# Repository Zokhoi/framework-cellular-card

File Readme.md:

## Framework Cellular Expansion Card

Compatible with Quectel cellular modules with same pinout as BG96.

This PCB design has been tested with EG912U-GL and EG95-EX modules. Other modules with compatible pinout will need different component values in various positions, consult the relevant hardware design information for details.

This PCB design is in alpha state, therefore gerber will not be provided and you should only proceed ordering at your own risk.

This PCB design does not incorporate built in antennas, and instead includes MHF-1 connectors for LTE main, diversity and GNSS. Thus you should pair your own 50 ohms impedance LTE antenna.

The PCB is 15mm longer than a regular expansion card PCB, a preliminary case design is provided.

### Board specifications

Size 26mm x 45mm, thickness 0.8mm, 4 layers, copper thickness 1oz 0.5oz 0.5oz 1oz, impedance controlled board with 0.2mm prepreg

### Compatible modem series comparison

| Modem series | Cellular standards | Downlink speed | Uplink speed | Cost   |
|--------------|--------------------|----------------|--------------|--------|
| EG95         | 4G, 3G, 2G         | 150 Mb/s       |  50 Mb/s     | \$\$   |
| EG91         | 4G, 2G             |  10 Mb/s       |   5 Mb/s     | \$     |
| BG96         | Cat-M, Cat-NB1     | 375 Kb/s       | 375 Kb/s     | \$\$   |

### License
This hardware design is licensed under [CERN-OHL-W V2 or later](License.txt).

### Board preview

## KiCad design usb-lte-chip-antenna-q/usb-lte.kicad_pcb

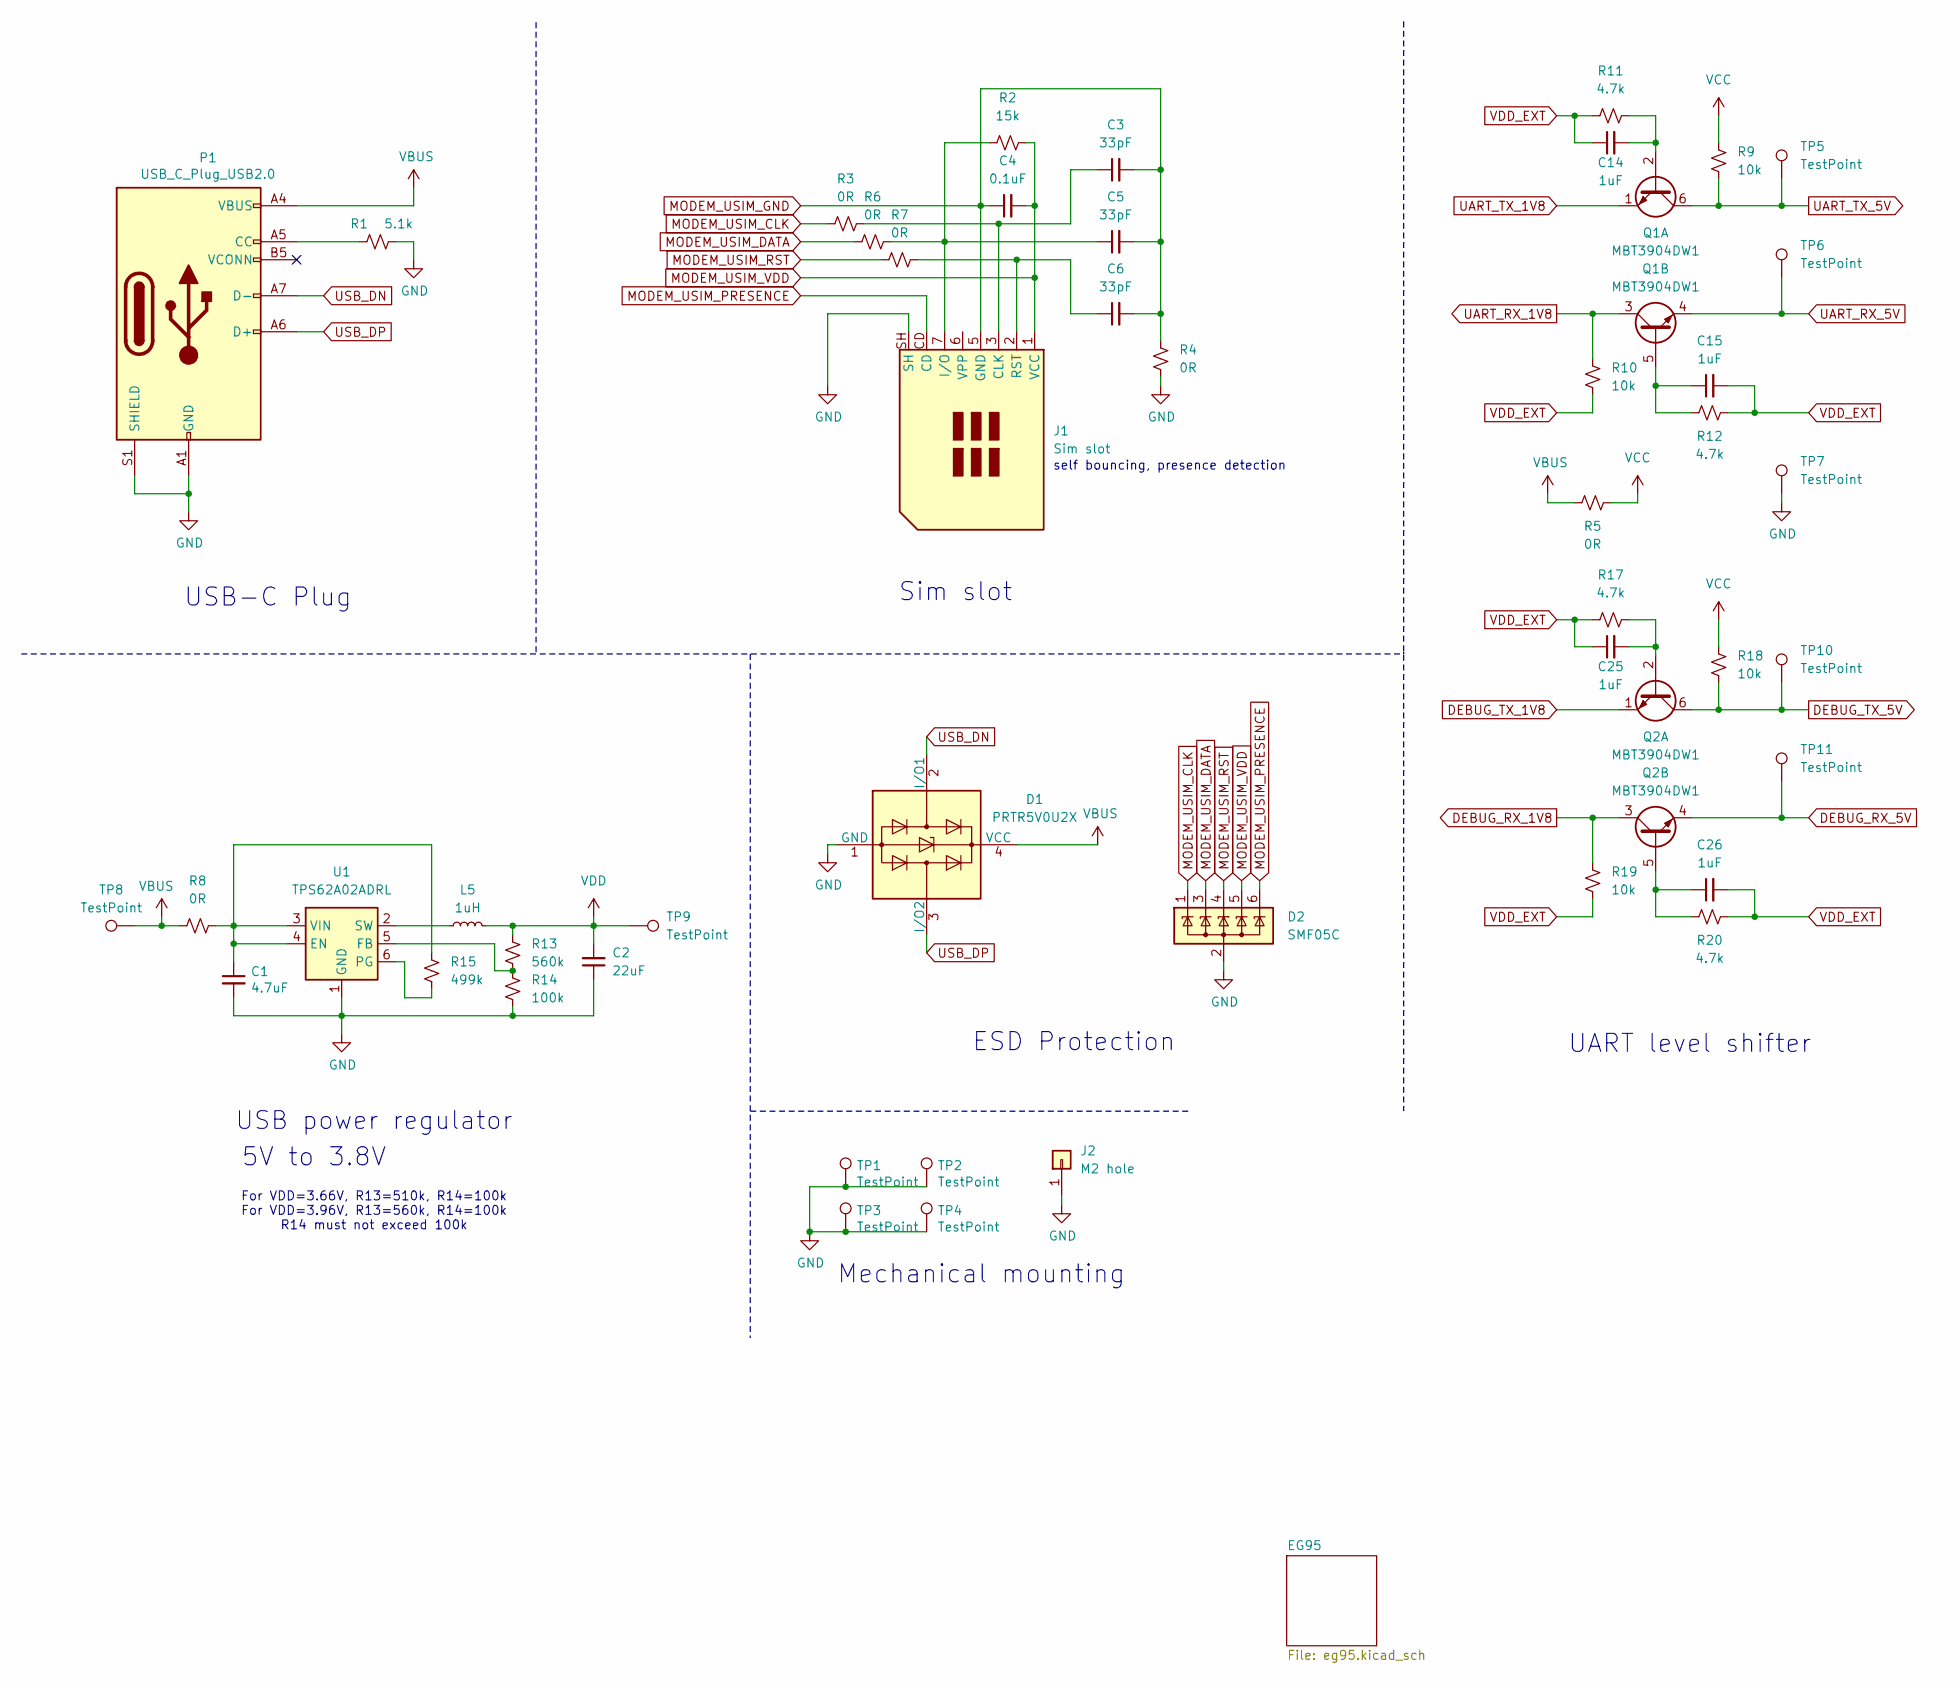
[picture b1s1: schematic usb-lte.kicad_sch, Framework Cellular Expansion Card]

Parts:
C1: 4.7uF; C_0805_2012Metric
C2: 22uF; C_0805_2012Metric
C3, C5, C6: 33pF; C_0402_1005Metric
C4: 0.1uF; C_0402_1005Metric
C14, C15, C25, C26: 1uF; C_0402_1005Metric
D1: PRTR5V0U2X; SOT-143
D2: SMF05C; SOT-363_SC-70-6
J1: Sim slot; SIM_Card_Self_Bounce_Detection
J2: M2 hole; M2_Mount_2.2mm_Pad_Minimal
L5: 1uH; L_APV_ANR252012
P1: USB_C_Plug_USB2.0; USB_C_Plug_Molex_105444
Q1, Q2: MBT3904DW1; SOT-363_SC-70-6
R1: 5.1k; R_0402_1005Metric_Pad0.72x0.64mm_HandSolder
R2: 15k; R_0402_1005Metric
R3, R6, R7, R8: 0R; R_0402_1005Metric_Pad0.72x0.64mm_HandSolder
R4, R5: 0R; R_0402_1005Metric
R9, R10, R18, R19: 10k; R_0402_1005Metric
R11, R12, R17, R20: 4.7k; R_0402_1005Metric
R13: 560k; R_0402_1005Metric
R14: 100k; R_0402_1005Metric
R15: 499k; R_0402_1005Metric
TP1, TP2, TP3, TP4: TestPoint; TestPoint_Pad_1.5x1.5mm
TP5, TP6, TP7, TP8, TP9, TP10, TP11: TestPoint; TestPoint_Pad_1mm
U1: TPS62A02ADRL; SOT-563

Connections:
DEBUG_RX_1V8: Q2.3 (C2), R19.1; also elsewhere on the board
DEBUG_RX_5V: Q2.4 (E2), TP11.1
DEBUG_TX_1V8: Q2.1 (E1); also elsewhere on the board
DEBUG_TX_5V: Q2.6 (C1), R18.2, TP10.1
GND: C1.2, C2.1, D1.1 (GND), D2.2 (A), J1.SH, J2.1, P1.A1 (GND), P1.A12 (GND), P1.B1 (GND), P1.B12 (GND), P1.S1 (SHIELD), R1.2, R4.2, R14.2, TP1.1, TP2.1, TP3.1, TP4.1, TP7.1, U1.1 (GND); also elsewhere on the board
MODEM_USIM_CLK: D2.1 (K), R3.1; also elsewhere on the board
MODEM_USIM_DATA: D2.3 (K), R6.1; also elsewhere on the board
MODEM_USIM_GND: C3.2, C4.1, C5.2, C6.2, J1.5 (GND), R4.1; also elsewhere on the board
MODEM_USIM_PRESENCE: D2.6 (K), J1.CD; also elsewhere on the board
MODEM_USIM_RST: D2.4 (K), R7.1; also elsewhere on the board
MODEM_USIM_VDD: C4.2, D2.5 (K), J1.1 (VCC), R2.2; also elsewhere on the board
unnamed: C3.1, J1.3 (CLK), R3.2
unnamed: C5.1, J1.7 (I/O), R2.1, R6.2
unnamed: C6.1, J1.2 (RST), R7.2
unnamed: P1.A5 (CC), R1.1
unnamed: C14.2, Q1.2 (B1), R11.2
unnamed: C15.1, Q1.5 (B2), R12.1
unnamed: C25.2, Q2.2 (B1), R17.2
unnamed: C26.1, Q2.5 (B2), R20.1
unnamed: C1.1, R8.2, R15.2, U1.3 (VIN), U1.4 (EN)
unnamed: R13.2, R14.1, U1.5 (FB)
unnamed: R15.1, U1.6 (PG)
unnamed: L5.1, U1.2 (SW)
UART_RX_1V8: Q1.3 (C2), R10.1; also elsewhere on the board
UART_RX_5V: Q1.4 (E2), TP6.1
UART_TX_1V8: Q1.1 (E1); also elsewhere on the board
UART_TX_5V: Q1.6 (C1), R9.2, TP5.1
USB_DN: D1.2 (I/O1), P1.A7 (D-); also elsewhere on the board
USB_DP: D1.3 (I/O2), P1.A6 (D+); also elsewhere on the board
VBUS: D1.4 (VCC), P1.A4 (VBUS), P1.A9 (VBUS), P1.B4 (VBUS), P1.B9 (VBUS), R5.1, R8.1, TP8.1; also elsewhere on the board
VCC: R5.2, R9.1, R18.1
VDD: C2.2, L5.2, R13.1, TP9.1; also elsewhere on the board
VDD_EXT: C14.1, C15.2, C25.1, C26.2, R10.2, R11.1, R12.2, R17.1, R19.2, R20.2; also elsewhere on the board

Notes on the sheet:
Sim slot
USB power regulator
For VDD=3.66V, R13=510k, R14=100k For VDD=3.96V, R13=560k, R14=100k R14 must not exceed 100k
Mechanical mounting
self bouncing, presence detection
USB-C Plug
ESD Protection
UART level shifter
5V to 3.8V

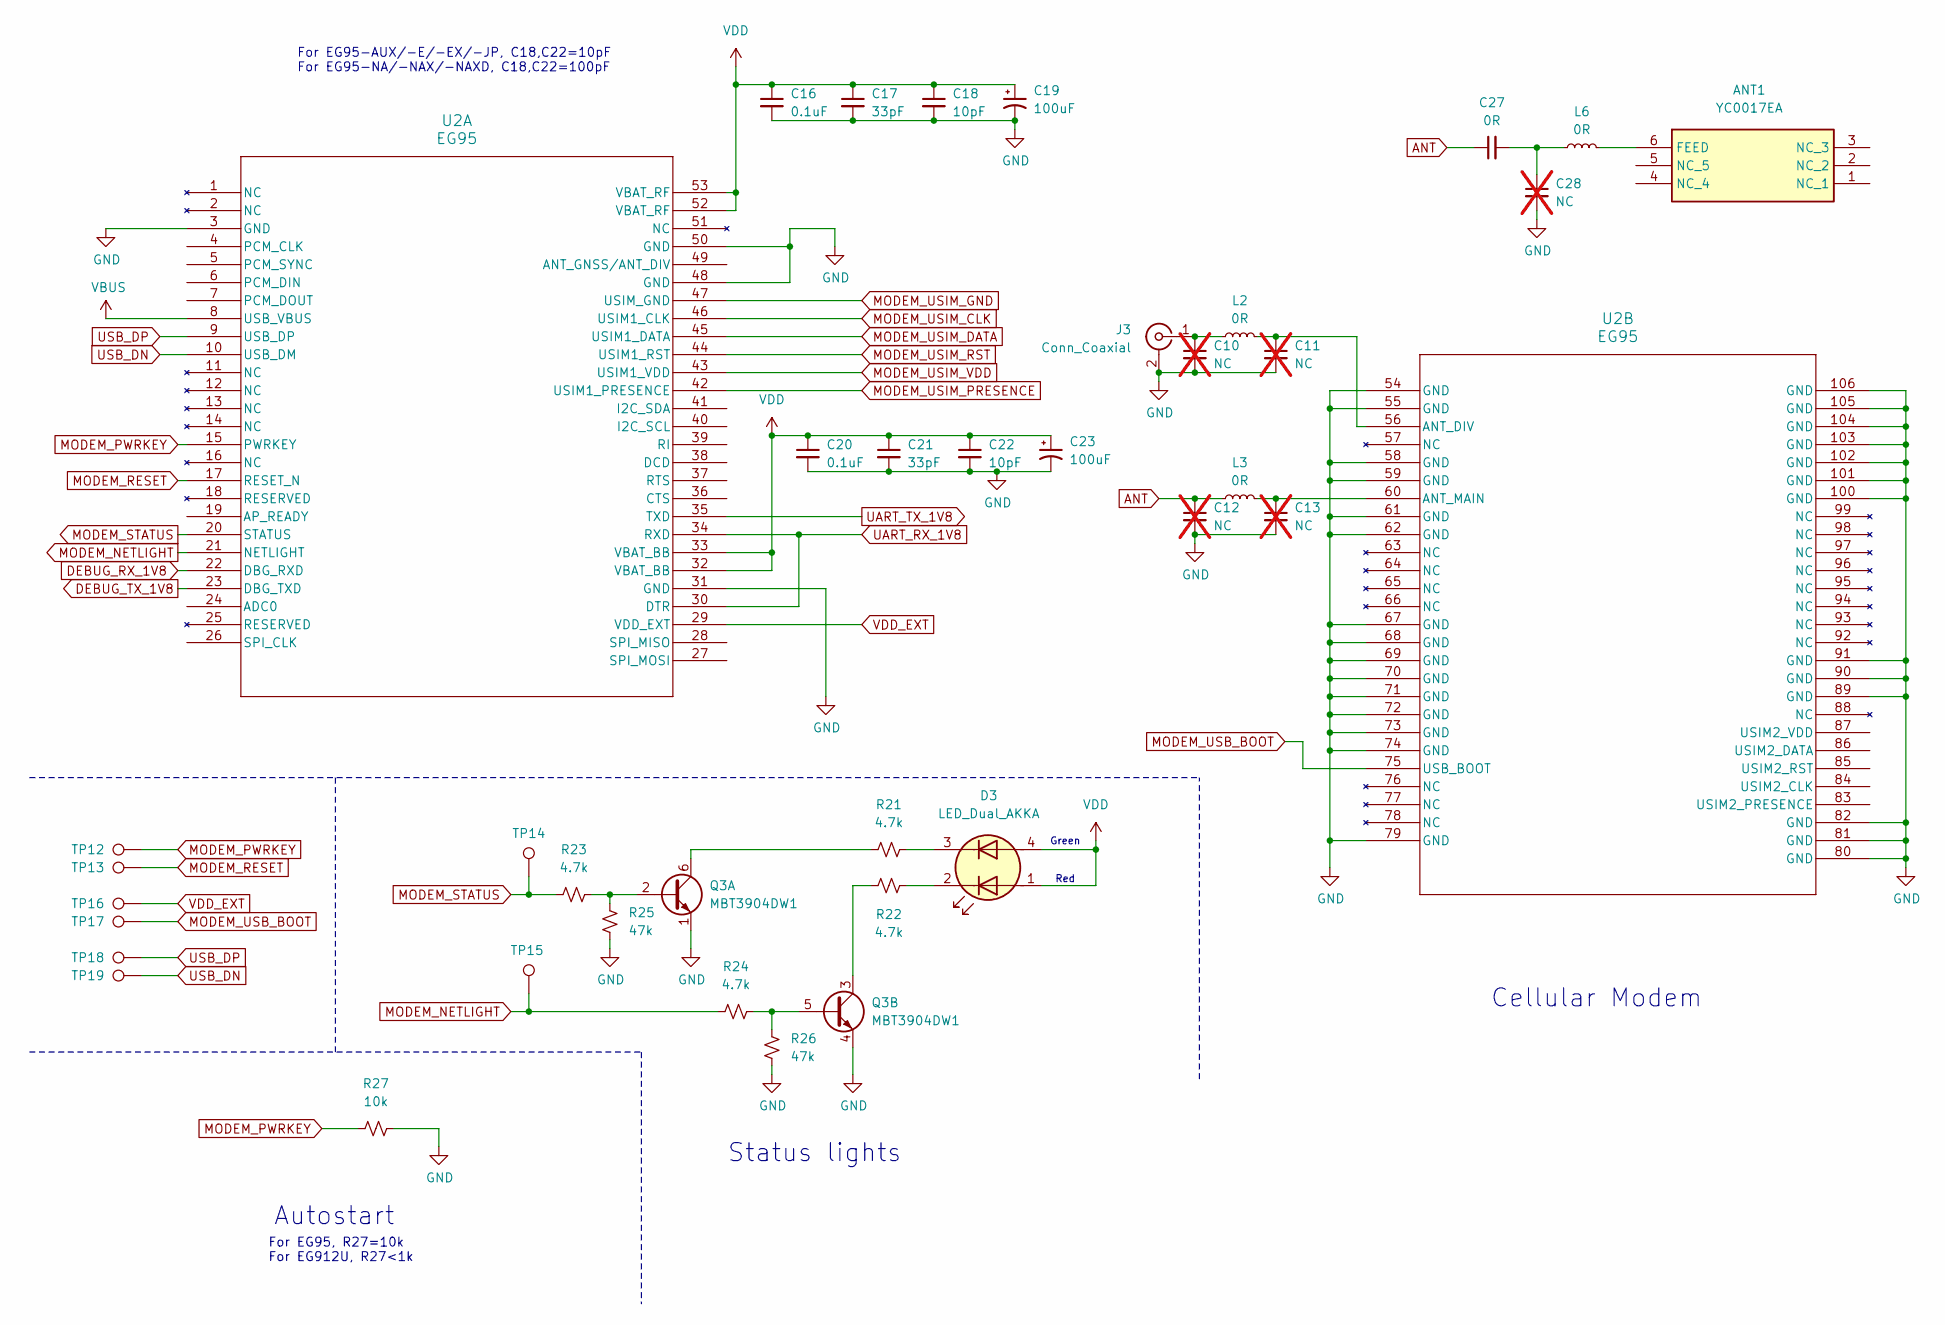
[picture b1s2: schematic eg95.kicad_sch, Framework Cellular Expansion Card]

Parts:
ANT1: YC0017EA; Mouser Part Number 277-YC0017EA
C10, C11, C12, C13, C28: NC; C_0402_1005Metric; not fitted
C16, C20: 0.1uF; C_0402_1005Metric
C17, C21: 33pF; C_0402_1005Metric
C18, C22: 10pF; C_0402_1005Metric
C19, C23: 100uF; CP_EIA-3528-21_Kemet-B
C27: 0R; C_0402_1005Metric
D3: LED_Dual_AKKA; LED_Dual_0805_4pin
J3: Conn_Coaxial; U.FL_Molex_MCRF_73412-0110_Vertical
L2, L3, L6: 0R; L_0402_1005Metric
Q3: MBT3904DW1; SOT-363_SC-70-6
R21, R22, R23, R24: 4.7k; R_0402_1005Metric
R25, R26: 47k; R_0402_1005Metric
R27: 10k; R_0402_1005Metric
TP12, TP13, TP14, TP15, TP16, TP17, TP18, TP19: TestPoint; TestPoint_Pad_1mm
U2: EG95; EG95_QWS

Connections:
ANT: C12.1, C27.1, L3.1
DEBUG_RX_1V8: U2.22 (DBG_RXD); also elsewhere on the board
DEBUG_TX_1V8: U2.23 (DBG_TXD); also elsewhere on the board
GND: C10.2, C11.2, C12.2, C13.2, C16.2, C17.2, C18.2, C19.2, C20.2, C21.2, C22.2, C23.2, C28.2, J3.2 (Ext), Q3.1 (E1), Q3.4 (E2), R25.1, R26.1, R27.1, U2.3 (GND), U2.31 (GND), U2.48 (GND), U2.50 (GND), U2.54 (GND), U2.55 (GND), U2.58 (GND), U2.59 (GND), U2.61 (GND), U2.62 (GND), U2.67 (GND), U2.68 (GND), U2.69 (GND), U2.70 (GND), U2.71 (GND), U2.72 (GND), U2.73 (GND), U2.74 (GND), U2.79 (GND), U2.80 (GND), U2.81 (GND), U2.82 (GND), U2.89 (GND), U2.90 (GND), U2.91 (GND), U2.100 (GND), U2.101 (GND), U2.102 (GND), U2.103 (GND), U2.104 (GND), U2.105 (GND), U2.106 (GND); also elsewhere on the board
MODEM_NETLIGHT: R24.2, TP15.1, U2.21 (NETLIGHT)
MODEM_PWRKEY: R27.2, TP12.1, U2.15 (PWRKEY)
MODEM_RESET: TP13.1, U2.17 (RESET_N)
MODEM_STATUS: R23.2, TP14.1, U2.20 (STATUS)
MODEM_USB_BOOT: TP17.1, U2.75 (USB_BOOT)
MODEM_USIM_CLK: U2.46 (USIM1_CLK); also elsewhere on the board
MODEM_USIM_DATA: U2.45 (USIM1_DATA); also elsewhere on the board
MODEM_USIM_GND: U2.47 (USIM_GND); also elsewhere on the board
MODEM_USIM_PRESENCE: U2.42 (USIM1_PRESENCE); also elsewhere on the board
MODEM_USIM_RST: U2.44 (USIM1_RST); also elsewhere on the board
MODEM_USIM_VDD: U2.43 (USIM1_VDD); also elsewhere on the board
unnamed: ANT1.6 (FEED), L6.2
unnamed: C27.2, C28.1, L6.1
unnamed: D3.2 (K1), R22.1
unnamed: D3.3 (K2), R21.1
unnamed: C10.1, J3.1 (In), L2.1
unnamed: Q3.2 (B1), R23.1, R25.2
unnamed: Q3.6 (C1), R21.2
unnamed: Q3.5 (B2), R24.1, R26.2
unnamed: Q3.3 (C2), R22.2
unnamed: C11.1, L2.2, U2.56 (ANT_DIV)
unnamed: C13.1, L3.2, U2.60 (ANT_MAIN)
UART_RX_1V8: U2.30 (DTR), U2.34 (RXD); also elsewhere on the board
UART_TX_1V8: U2.35 (TXD); also elsewhere on the board
USB_DN: TP19.1, U2.10 (USB_DM); also elsewhere on the board
USB_DP: TP18.1, U2.9 (USB_DP); also elsewhere on the board
VBUS: U2.8 (USB_VBUS); also elsewhere on the board
VDD: C16.1, C17.1, C18.1, C19.1, C20.1, C21.1, C22.1, C23.1, D3.1 (A1), D3.4 (A2), U2.32 (VBAT_BB), U2.33 (VBAT_BB), U2.52 (VBAT_RF), U2.53 (VBAT_RF); also elsewhere on the board
VDD_EXT: TP16.1, U2.29 (VDD_EXT); also elsewhere on the board

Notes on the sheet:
Green
For EG95-AUX/-E/-EX/-JP, C18,C22=10pF For EG95-NA/-NAX/-NAXD, C18,C22=100pF
Cellular Modem
Autostart
For EG95, R27=10k For EG912U, R27<1k
Red
Status lights

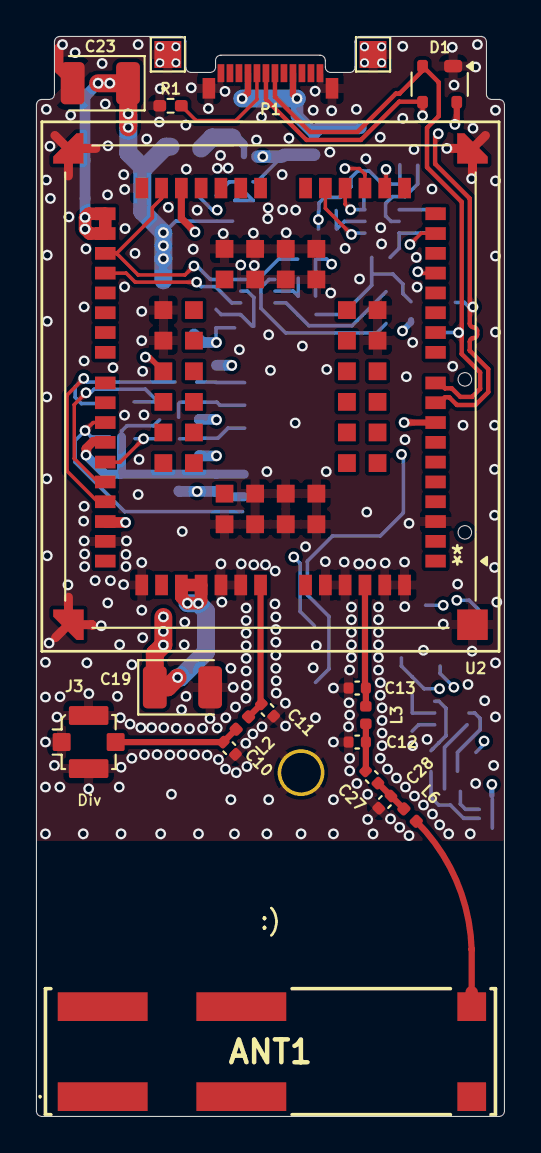
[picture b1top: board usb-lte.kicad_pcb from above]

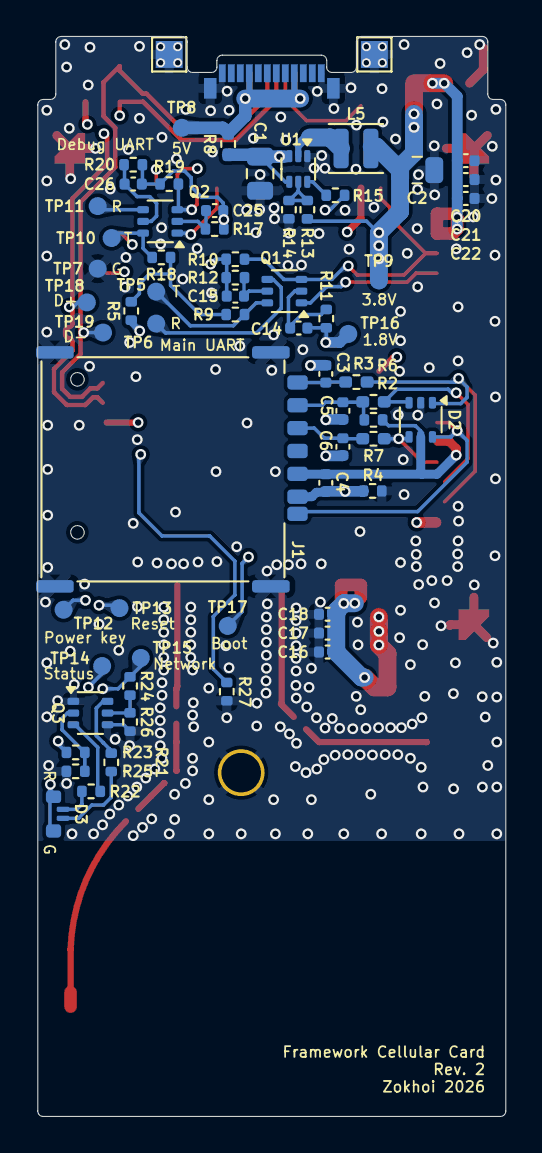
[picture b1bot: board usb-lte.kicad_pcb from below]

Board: 4 copper layers, 26.0 x 60.0 mm, 86 parts (66 on the bottom side), 50 nets.

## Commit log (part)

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2025-03-26 init
2025-03-26 Fix symbol
2025-03-26 Mark pi network caps as NC
2025-03-26 separate gnd and sim gnd
2025-03-27 added positioning NPTH for sim slot
2025-03-28 match usb 90 ohm impedance
2025-03-30 Use main power rail for gnss antenna
2025-04-05 Use SMPS and 3.8V for module
2025-04-05 Make USB C 2.0 reversible
2025-04-05 Minor changes
2025-04-05 Add TVS diode for sim slot
2025-04-06 Moved TVS diode closer to sim slot
2025-04-09 Add debug uart breakout
2025-04-09 Add various test points
2025-04-19 Add status lights and usb boot key
2025-04-21 Update 3d models
2025-04-21 Update test points
2025-05-04 Remove USB boot key, add autostart pull down
2025-05-05 Fix SMPS chip variant number
2025-09-16 Add case design
